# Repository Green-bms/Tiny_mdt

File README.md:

# Tiny_mdt
A useful tiny gadget! <br>  
Youtube video: https://www.youtube.com/embed/fY5Y1o6QoCc?si=GF92eTSO-mVCjJeZ <br> 
<br> 
Tiny mdt is a small electronic gadget that measures environmental data and shows it on a small 0.96" OLED display. 
The data is acquired and processed by an ATtiny85 microcontroller.<br> 
) <br> 
The device is powered by a 3v CR2032 coin cell
the card only works when the power button is pressed and turns off when released.
So most of the time the device stays off, saving energy.
According to my calculations, with moderate use, the battery should last about 10-12 months.
I created the software with Arduino IDE. The big challenge was to find the lightest libraries to fit in the limited memory of the ATtiny85.
The project is available in 2 versions, with the same PCB (only the sensors to be used and the software to be loaded into the microcontroller change) <br>
## Type 1: htt
) <br> 
This variant uses the HTU21D sensor which measures humidity and ambient temperature.
Furthermore, the temperature of an object is also detected using the MLX90614 infrared thermometer. <br> 
) <br>
## Type 2: htp
) <br> 
This is a small portable weather station in the palm of your hand!
The board uses the excellent BME280 sensor which measures humidity, temperature and barometric pressure.<br> 
) <br>
## Do it yourself
This project is completely open source and is very simple to create. <br>
) <br>
I deliberately used tht components to facilitate soldering.<br>
) <br>
The ATtiny85 microcontroller is socket mounted, so it can be easily removed and programmed using the maker's favorite programmer.
For example, I used the "Wemos as ISP" programmer that you find here: https://github.com/Green-bms/Wemos-as-ISP <br>
) <br>

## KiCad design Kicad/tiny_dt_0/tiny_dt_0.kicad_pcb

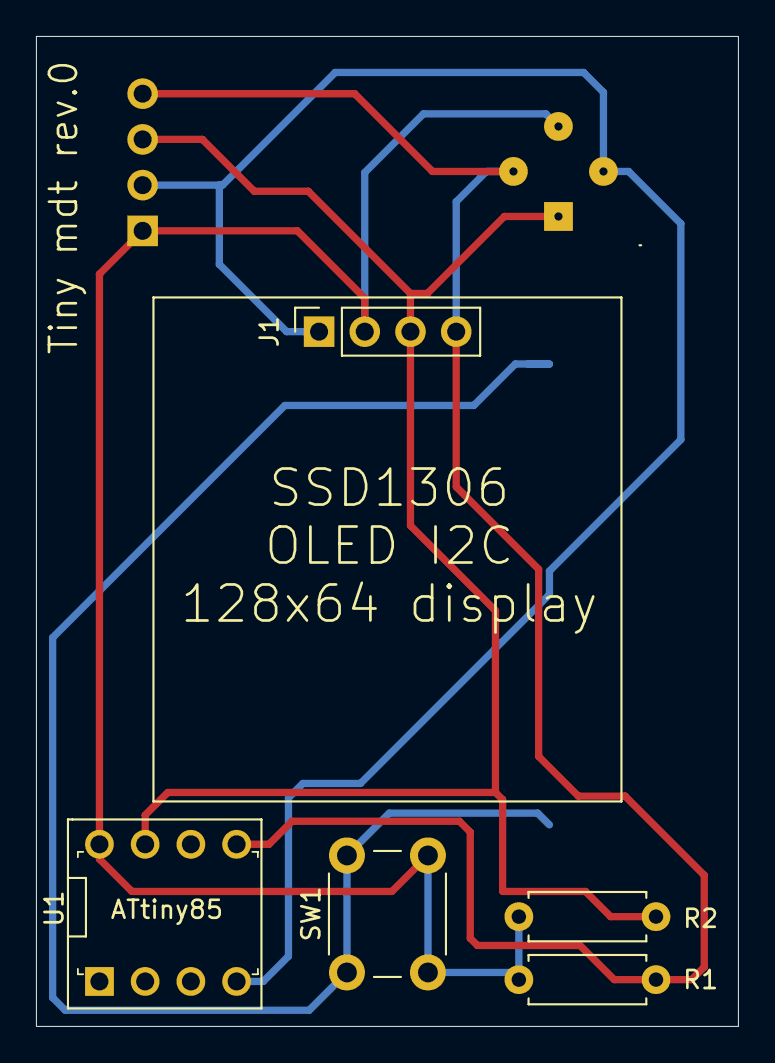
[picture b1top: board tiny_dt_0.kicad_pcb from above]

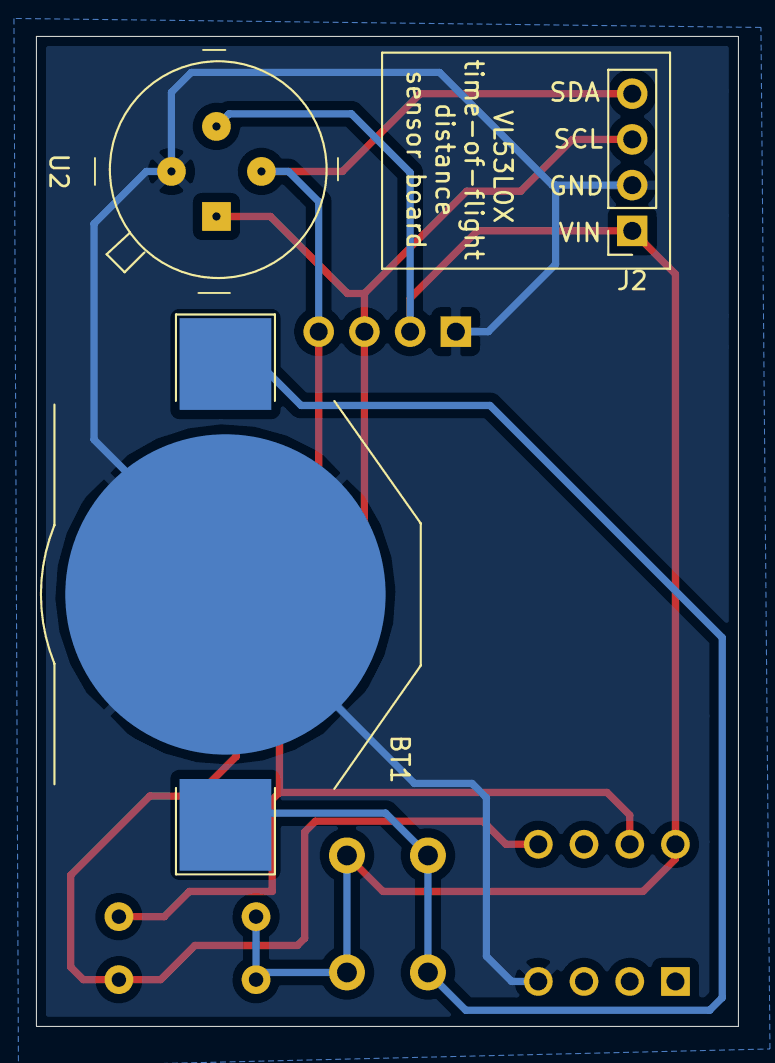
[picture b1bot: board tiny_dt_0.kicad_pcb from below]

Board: 2 copper layers, 39.0 x 55.0 mm, 8 parts (3 on the bottom side), 5 nets.

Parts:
BT1: Battery Cell CR2032; BatteryHolder_Keystone_3002_1x2032
J1: SSD1306 OLED I2C 128x64 display; PinSocket_1x04_P2.54mm_Vertical
J2: VL53L0X time-of-flight distance sensor board; PinSocket_1x04_P2.54mm_Vertical
R1, R2: 4.7K; R_Axial_DIN0207_L6.3mm_D2.5mm_P7.62mm_Horizontal
SW1: SW_Push_Dual; SW_PUSH_6mm
U1: ATTINY85-20PU; DIP-8_W7.62mm
U2: MLX90614ESF-BAA-000-TU; TO-39-4

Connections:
/3V: J1.2, J2.1, R1.1, R2.1, SW1.2, U1.8, U2.3
/GND: BT1.2, J1.1, J2.2, U1.4, U2.4
/SCL: J1.3, J2.3, R2.2, U1.7, U2.1
/SDA: J1.4, J2.4, R1.2, U1.5, U2.2
unnamed: BT1.1, SW1.1
